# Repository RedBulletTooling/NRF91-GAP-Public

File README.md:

This is a project by Matthijs Vogel and Luc Pluimakers.

# Concept

NRF91 General Attack Platform, or GAP for short. The goal of the GAP module was to create a modular base from which we could design various types of listening devices. It serves as the central brain and communications hub, as well as the module that regulates power, eliminating the need for a complex PSU per purpose. We have decided to release this design to the public, as there is no benefit in keeping it private, and we believe it can add value to the public space.

## NRF91GAP

The board itself. When designing it, the decision was made to make it thin—really thin. This is because most devices and locations have enough tolerance to hide something as long as it's thin enough. With this design, we achieved a thickness of 1.5mm. We used special LDOs (Low Dropout Regulators) with a wide operating range (20V to 1.8V)—one for powering the NRF91 and another for powering the external board, both outputting 5V. This way, it can be implemented in a car or connected directly to a laptop battery, making it an always-on system, regardless of whether the host machine is turned off. Perfect for pre-boot DMA injection! Almost all of the I/O of the NRF91 is directly connected to the ribbon cable, and they can be left floating if not needed. It uses a Tag-Connect cable for programming. It's a cool concept, and we hope some of you find a use for it!

## Breakout Example

We have included an example breakout we designed for the NRF91GAP. The purpose of this board is to monitor the keystrokes of an XPS 15 laptop by sitting between the ribbon cable of the laptop's keyboard and the keyboard controller. It connects through a standard Molex ribbon cable, which coincides with the connector on the NRF91GAP. The breakout board itself is a flex PCB with specific rigid parts and is designed in such a way that it fits perfectly within the laptop. The flex PCB cable interfaces directly with a board, as if it were the ribbon cable. This demonstrates the capability of the NRF91GAP. You could do this with anything since it directly interfaces with the I/O ports of the NRF91 chip, and like what we did here, you can adjust voltages and translations on the breakout board.

## Notes

This is a concept design. It is not yet in production. We are 80% confident that this will work as-is, but there are still some things to keep in mind:

1. The current version of the board has not been produced yet but is an improved version compared to the one in the pictures, as the earlier version had issues with BGA pads and a 0.3mm PCB thickness.
2. It is a 2-layer PCB with a relatively expensive design, as it heavily relies on thin traces, tented vias, and vias in pads.
3. The breakout board is a non-functional prototype. It needs revisions in multiple areas, but it shows the concept's capabilities.
4. The GAP board uses a special MHF4 antenna. If possible, use an MHF4L.

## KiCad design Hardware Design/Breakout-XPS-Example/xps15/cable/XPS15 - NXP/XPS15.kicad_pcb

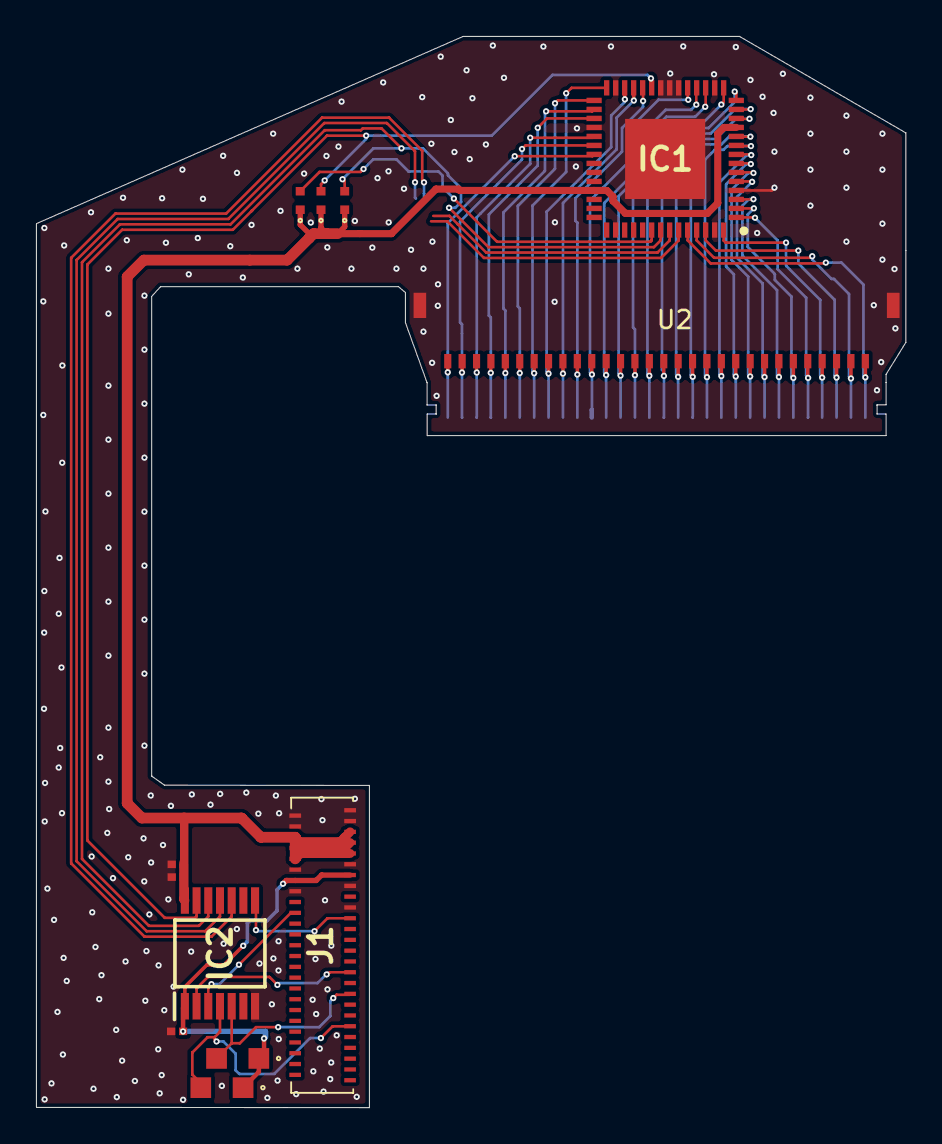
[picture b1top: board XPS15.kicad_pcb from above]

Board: 2 copper layers, 48.3 x 59.5 mm, 13 parts (1 on the bottom side), 43 nets.

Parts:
C1, C2: GRM033R60J104KE19J; CAPC0603X33N
C3: GRM033R60J105MEA2D; CAPC0603X33N
IC1: PCA9698BS,118; QFN50P800X800X100-57N-D
IC2: NTS0304EPWJ; SOP65P640X110-14N
J1: 504740-5100; 5047405100
R1, R2: ERA-6ARW472V; ERA6A__0805_
R3, R4: ERA-2ARC112X; ERA2A__0402_
R5: ERA-2AED202X; ERA2A__0402_
U1: XPS-FLEX; Flex
U2: XPS15-Con; FPC-XPS15

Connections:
+1V8: C1.2, IC2.1, J1.38, J1.39, R1.1, R2.1
GND: C1.1, C2.2, C3.1, IC1.4, IC1.16, IC1.20, IC1.21, IC1.22, IC1.27, IC1.32, IC1.44, IC1.55, IC1.57, IC2.7, J1.33, J1.36, J1.37, J1.40, J1.41, J1.48, J1.49, J1.50, J1.51, U2.31, U2.32
INT: IC1.48, R5.2
OE: IC1.23, IC2.13, R3.2
OE-C: IC2.2, J1.21
OE-NTS: IC2.8, J1.31
SCL: IC1.51, IC2.10
SCL-C: IC2.5, J1.17, R1.2
SDA: IC1.50, IC2.11
SDA-C: IC2.4, J1.11, R2.2
VCC: C2.1, C3.2, IC1.11, IC1.39, IC2.14, J1.42, J1.43, J1.44, J1.45, J1.46, J1.47, R3.1, R4.1, R5.1
pin1: IC1.52, U1.1, U2.1
pin2: IC1.53, U1.2, U2.2
pin3: IC1.54, U1.3, U2.3
pin4: IC1.56, U1.4, U2.4
pin5: IC1.1, U1.5, U2.5
pin6: IC1.2, U1.6, U2.6
pin7: IC1.3, U1.7, U2.7
pin8: IC1.5, U1.8, U2.8
pin9: IC1.6, U1.9, U2.9
pin10: IC1.7, U1.10, U2.10
pin11: IC1.8, U1.11, U2.11
pin12: IC1.9, U1.12, U2.12
pin13: IC1.10, U1.13, U2.13
pin14: IC1.12, U1.14, U2.14
pin15: IC1.13, U1.15, U2.15
pin16: IC1.14, U1.16, U2.16
pin17: IC1.15, U1.17, U2.17
pin18: IC1.17, U1.18, U2.18
pin19: IC1.18, U1.19, U2.19
pin20: IC1.19, U1.20, U2.20
pin21: IC1.24, U1.21, U2.21
pin22: IC1.25, U1.22, U2.22
pin23: IC1.26, U1.23, U2.23
pin24: IC1.28, U1.24, U2.24
pin25: IC1.29, U1.25, U2.25
pin26: IC1.30, U1.26, U2.26
pin27: IC1.31, U1.27, U2.27
pin28: IC1.33, U1.28, U2.28
pin29: IC1.34, U1.29, U2.29
pin30: IC1.35, U1.30, U2.30
reset: IC1.49, IC2.12, R4.2
reset-C: IC2.3, J1.32

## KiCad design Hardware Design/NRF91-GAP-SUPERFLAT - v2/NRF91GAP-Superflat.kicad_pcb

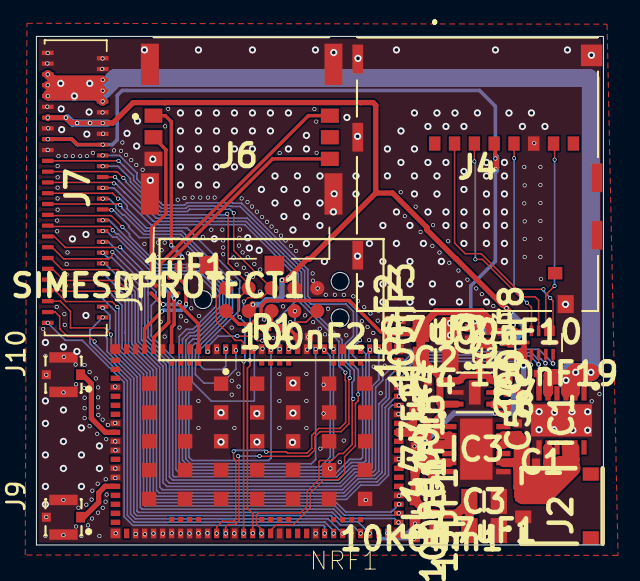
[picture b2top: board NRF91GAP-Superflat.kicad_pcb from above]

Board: 2 copper layers, 31.5 x 28.2 mm, 41 parts (0 on the bottom side), 61 nets.

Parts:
1uF1: GRM033C80J105ME05D; CAPC0603X33N
4.7uF1, 4.7uF2: GRM035R60J475ME15D; CAPC0603X55N
10KOhm1: ERA-1AEB103C; RESC0603X26N
15pF1, 15pF2: 885392004002; CAPC0603X33N
47uF1, 47uF2: GRM219R60J476ME44D; CAPC2012X95N
100nF1, 100nF2, 100nF3, 100nF4, 100nF8, 100nF10, 100nF15, 100nF19: GRM033R60J104KE19J; CAPC0603X33N
C1, C4, C5, C6, C8, C9: GRM033C80J105ME05D; CAPC0603X33N
C2, C3: GRM219R60J476ME44D; CAPC2012X95N
C7: GCM033R71A103KA03D; CAPC0603X33N
FL1: MMZ1005S121HTD25; BEADC1005X55N
IC1, IC3: LT1763IDE-5#PBF; SON50P300X400X80-13N-D
IC5: MIC5303-3.3YMT-TR; SON50P160X120X60-5N-D
J2: 78171-0002
J4: DM3NW-SF-PEJ_800_; DM3NWSFPEJ800
J5: TC2050-IDC-NL; TAG-CONNECT_TC2050-IDC-NL
J6: 104224-0820; 1042240820
J7: 504740-5100; 5047405100
J9, J10: RECE-20449-001E-01; CONN_RECE-20449-001E-01
NRF1: NRF9160-SICA-B1A-R; XCVR_NRF9160-SICA-R
R1: CR0201AFW-1001GLF; RESC0603X26N
SIMESDPROTECT1: CM1402-03CP; CM140203CP
U2: MIC5325-1.8YMT-TR
U3: TXB0104RUT; Texas_R_PUQFN-N12

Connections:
+1V8: 4.7uF2.1, 100nF4.1, 100nF8.1, C8.2, J5.2, J7.13, J7.14, NRF1.12, U2.4, U3.1, U3.12
+3V3: 100nF10.1, C9.2, IC5.4, J4.C4, J7.17, J7.18, U3.11
+5V: 100nF19.1, IC1.2, IC1.3, IC1.5, J7.5, J7.6, J7.7, J7.8, J7.9, J7.10
+VDC: C1.2, C5.2, IC1.8, IC1.10, IC1.11, IC3.8, IC3.10, IC3.11, J2.2
CD\DAT3-CS: J4.C2, U3.7
CLK: J4.C5, U3.10
CLKSIM: NRF1.46, SIMESDPROTECT1.C2
CMD\DI-MOSI: J4.C3, U3.9
CS: J7.38, NRF1.23, U3.5
DAT0\DO-MISO: J4.C7, U3.8
DATSIM: NRF1.48, SIMESDPROTECT1.C3
GND: 1uF1.1, 4.7uF1.2, 4.7uF2.2, 15pF1.2, 15pF2.2, 47uF1.1, 47uF2.2, 100nF1.2, 100nF2.2, 100nF3.2, 100nF4.2, 100nF8.2, 100nF10.2, C1.1, C2.1, C3.1, C4.1, C5.1, C6.2, C7.2, C8.1, C9.1, IC1.7, IC1.13, IC3.7, IC3.13, IC5.2, IC5.5, J2.1, J4.C6, J4.G1, J4.G2, J4.G3, J4.G4, J4.G5, J4.G6, J4.G7, J5.6, J5.7, J6.G1, J6.G2, J6.G3, J6.G4, J6.S4, J7.1, J7.2, J7.3, J7.4, J7.11, J7.12, J7.15, J7.16, J7.19, J9.2, J9.3, J9.4, J10.2, J10.3, J10.4, NRF1.1, NRF1.5, NRF1.9, NRF1.14, NRF1.17, NRF1.21, NRF1.27, NRF1.31, NRF1.36, NRF1.41, NRF1.44, NRF1.47, NRF1.50, NRF1.52, NRF1.56, NRF1.60, NRF1.62, NRF1.63, NRF1.65, NRF1.66, NRF1.72, NRF1.74, NRF1.75, NRF1.76, NRF1.77, NRF1.78, NRF1.79, NRF1.80, NRF1.81, NRF1.82, NRF1.85, NRF1.90, NRF1.94, NRF1.98, NRF1.103_1, NRF1.103_2, NRF1.103_3, NRF1.103_4, NRF1.103_5, NRF1.103_6, NRF1.103_7, NRF1.103_8, NRF1.103_9, NRF1.103_10, NRF1.103_11, NRF1.103_12, NRF1.103_13, NRF1.103_14, NRF1.103_15, NRF1.103_16, NRF1.103_17, NRF1.103_18, NRF1.103_19, NRF1.103_20, NRF1.103_21, NRF1.103_22, NRF1.103_23, NRF1.103_24, NRF1.103_25, NRF1.103_26, NRF1.103_27, NRF1.103_28, NRF1.103_29, NRF1.103_30, NRF1.103_31, NRF1.103_32, NRF1.103_33, NRF1.103_34, NRF1.103_35, SIMESDPROTECT1.B1, SIMESDPROTECT1.B2, U2.2, U2.7, U3.6
MISO: J7.39, NRF1.20, U3.4
MOSI: J7.40, NRF1.19, U3.3
NRESET: J5.3, R1.1
unnamed: 4.7uF1.1, NRF1.13
unnamed: 10KOhm1.2, NRF1.101
unnamed: 100nF2.1, NRF1.32, R1.2
unnamed: 100nF15.2, IC3.6
unnamed: 100nF19.2, IC1.6
unnamed: C7.1, U2.5
unnamed: J6.S2, SIMESDPROTECT1.A1
unnamed: J6.S3, SIMESDPROTECT1.A2
unnamed: J6.S6, SIMESDPROTECT1.A3
unnamed: J9.1, NRF1.67
unnamed: J10.1, NRF1.61
unnamed: NRF1.6, NRF1.7, NRF1.8, NRF1.10, NRF1.11, NRF1.51, NRF1.68, NRF1.69, NRF1.70, NRF1.71, NRF1.73, NRF1.104, NRF1.105, NRF1.106, NRF1.107, NRF1.108, NRF1.109, NRF1.110, NRF1.111, NRF1.112, NRF1.113, NRF1.114, NRF1.115, NRF1.116, NRF1.117, NRF1.118, NRF1.119, NRF1.120, NRF1.121, NRF1.122, NRF1.123, NRF1.124, NRF1.125, NRF1.126, NRF1.127
P0: J7.51, NRF1.95
P1: J7.50, NRF1.96
P2: J7.49, NRF1.97
P3: J7.48, NRF1.99
P4: J7.47, NRF1.100
P5: J7.46, NRF1.2
P6: J7.45, NRF1.3
P7: J7.44, NRF1.4
P8: J7.43, NRF1.15
P9: J7.42, NRF1.16
P10: J7.41, NRF1.18, U3.2
P14: J7.37, NRF1.24
P15: J7.36, NRF1.25
P16: J7.35, NRF1.26
P17: J7.34, NRF1.28
P18: J7.33, NRF1.29
P19: J7.32, NRF1.30
P20: J7.31, NRF1.35
P21: J7.30, NRF1.37
P22: J5.10, J7.29, NRF1.38
P23: J7.28, NRF1.39
P24: J7.27, NRF1.40
P25: J7.26, NRF1.42
P26: J7.25, NRF1.83
P27: J7.24, NRF1.84
P28: J5.9, J7.23, NRF1.86
P29: J5.8, J7.22, NRF1.87
P30: J7.21, NRF1.88
P31: J7.20, NRF1.89
RSTSIM: NRF1.43, SIMESDPROTECT1.C1
SIM1.8v: 1uF1.2, J6.S1, NRF1.49, SIMESDPROTECT1.A4
SWDCLK: J5.4, NRF1.33
SWDIO: J5.5, NRF1.34
VCC: 10KOhm1.1, 15pF1.1, 15pF2.1, 47uF1.2, 47uF2.1, 100nF1.1, 100nF3.1, 100nF15.1, C2.2, C3.2, C4.2, C6.1, FL1.1, FL1.2, IC3.2, IC3.3, IC3.5, IC5.1, IC5.3, J5.1, NRF1.22, NRF1.102, U2.1, U2.3, U2.6

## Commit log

2024-12-08 Release
